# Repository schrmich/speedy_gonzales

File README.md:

# speedy_gonzales
A small unique robot plattform with AVR microcontroller programmed in C.

1	Vorwort
Der Roboter „Speedy-bot“ ist ein kleiner frei in C programmierbarer Lern Roboter. Er soll in der Lage sein, verschiedene Aufgaben selbstständig zu erledigen, dazu gehören das Lösen von Linienlabyrinthen. Dazu ist er mit einer Reihe von 5 analogen IR-Reflektions Sensoren an der Unterseite ausgestattet, sowie zwei optische Motorencoder. Zur Kommunikation wird ein HC-06 Bluetooth Modul verwendet. Als Antrieb dienen zwei DC-Getriebemotoren.
Die Elektronik ist komplett in SMD aufgebaut und als Steuercomputer werkelt ein Atmega644PA. 

2	Aufgaben/ Ziele
Hier eine kleine  Liste mit möglichen Aufgaben die Spirit bewältigen soll:
•	Einfaches Linienfolgen PID Regler mit max. Geschwindigkeit
•	Linienfolgen mit Unterbrechungen, Kreuzungen, Hindernissen, etc…
•	Joghurt Sumo
•	Fernsteuerung über PC/ Smartphone
3	Mechanik
Der Roboter hat die Abmessungen von 100x75 mm und hat zwei Antriebsräder mit zwei Stützrädern vorn und hinten. Sein Gesamtgewicht mit Akkus beläuft sich auf 85g.

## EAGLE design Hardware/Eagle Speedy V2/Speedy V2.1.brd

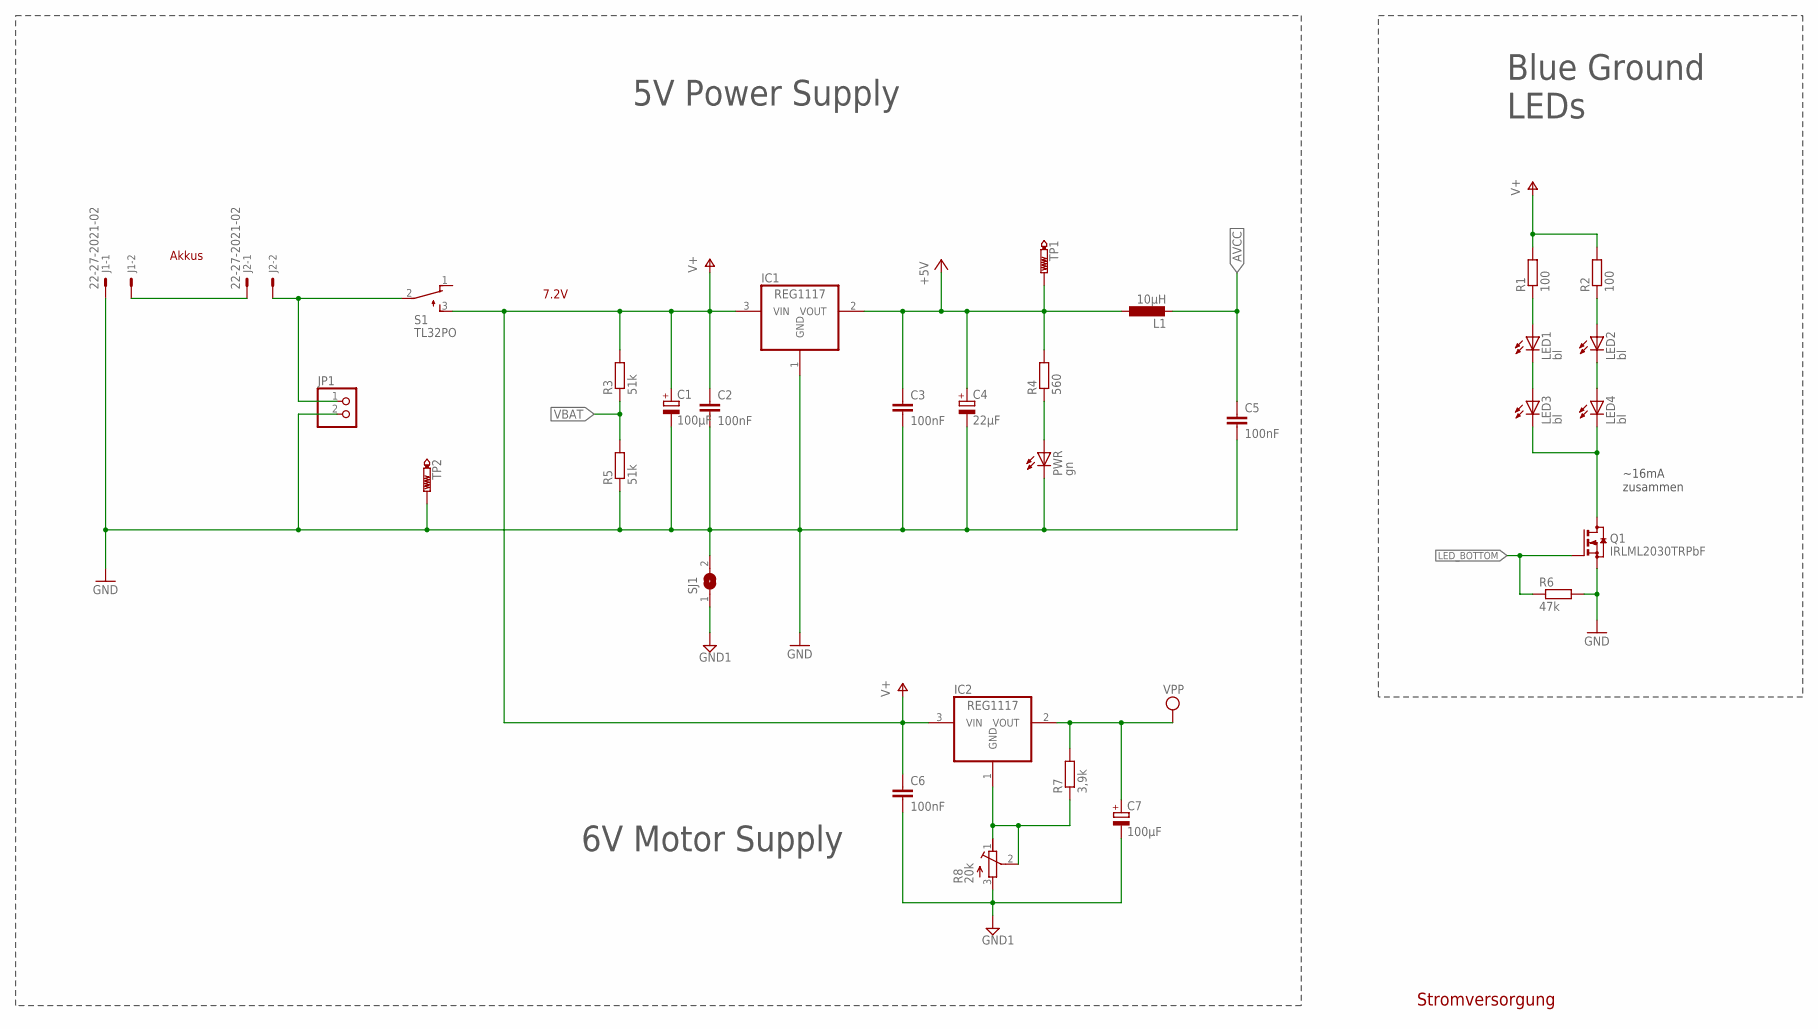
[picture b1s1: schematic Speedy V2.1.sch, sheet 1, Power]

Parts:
C1, C7: 100µF; PANASONIC_D
C2, C3, C5, C6: 100nF; C0805
C4: 22µF; PANASONIC_B
IC1, IC2: REG1117; SOT223
J1, J2: 22-27-2021-02; 6410-02
JP1: PINHD-1X2; 1X02
L1: 10µH; C1210K
LED1, LED2, LED3, LED4: bl; CHIPLED_0805
PWR: gn; CHIPLED_0805
Q1: IRLML2030TRPbF; SOT23
R1, R2: 100; R0805
R3, R5: 51k; R0805
R4: 560; R0805
R6: 47k; R0805
R7: 3,9k; R0805
R8: 20k; RTRIM3314G
S1: TL32PO; TL3XPO
SJ1: SJ
TP1: PTR1B1,27; B1,27
TP2: PTR1PAD1-13; P1-13

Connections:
+5V: C3.1, C4.+, IC1.2 (VOUT), L1.1, R4.2, TP1.TP; also elsewhere on the board
AVCC: C5.1, L1.2; also elsewhere on the board
GND: C1.-, C2.2, C3.2, C4.-, C5.2, IC1.1 (GND), J1.1, JP1.2, PWR.C, Q1.2 (S), R5.1, R6.2, SJ1.2, TP2.TP; also elsewhere on the board
GND1: C6.2, C7.-, R8.3 (A), SJ1.1; also elsewhere on the board
LED_BOTTOM: Q1.1 (G), R6.1; also elsewhere on the board
unnamed: J1.2, J2.1
unnamed: PWR.A, R4.1
unnamed: J2.2, JP1.1, S1.2
unnamed: LED3.C, LED4.C, Q1.3 (D)
unnamed: LED1.A, R1.1
unnamed: LED1.C, LED3.A
unnamed: LED2.C, LED4.A
unnamed: LED2.A, R2.1
unnamed: IC2.1 (GND), R7.1, R8.1 (E), R8.2 (S)
V+: C1.+, C2.1, C6.1, IC1.3 (VIN), IC2.3 (VIN), R1.2, R2.2, R3.2, S1.3 (S); also elsewhere on the board
VBAT: R3.1, R5.2; also elsewhere on the board
VPP: C7.+, IC2.2 (VOUT), R7.2; also elsewhere on the board

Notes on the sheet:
Stromversorgung
5V Power Supply
Blue Ground LEDs
Akkus
7.2V
~16mA zusammen
6V Motor Supply

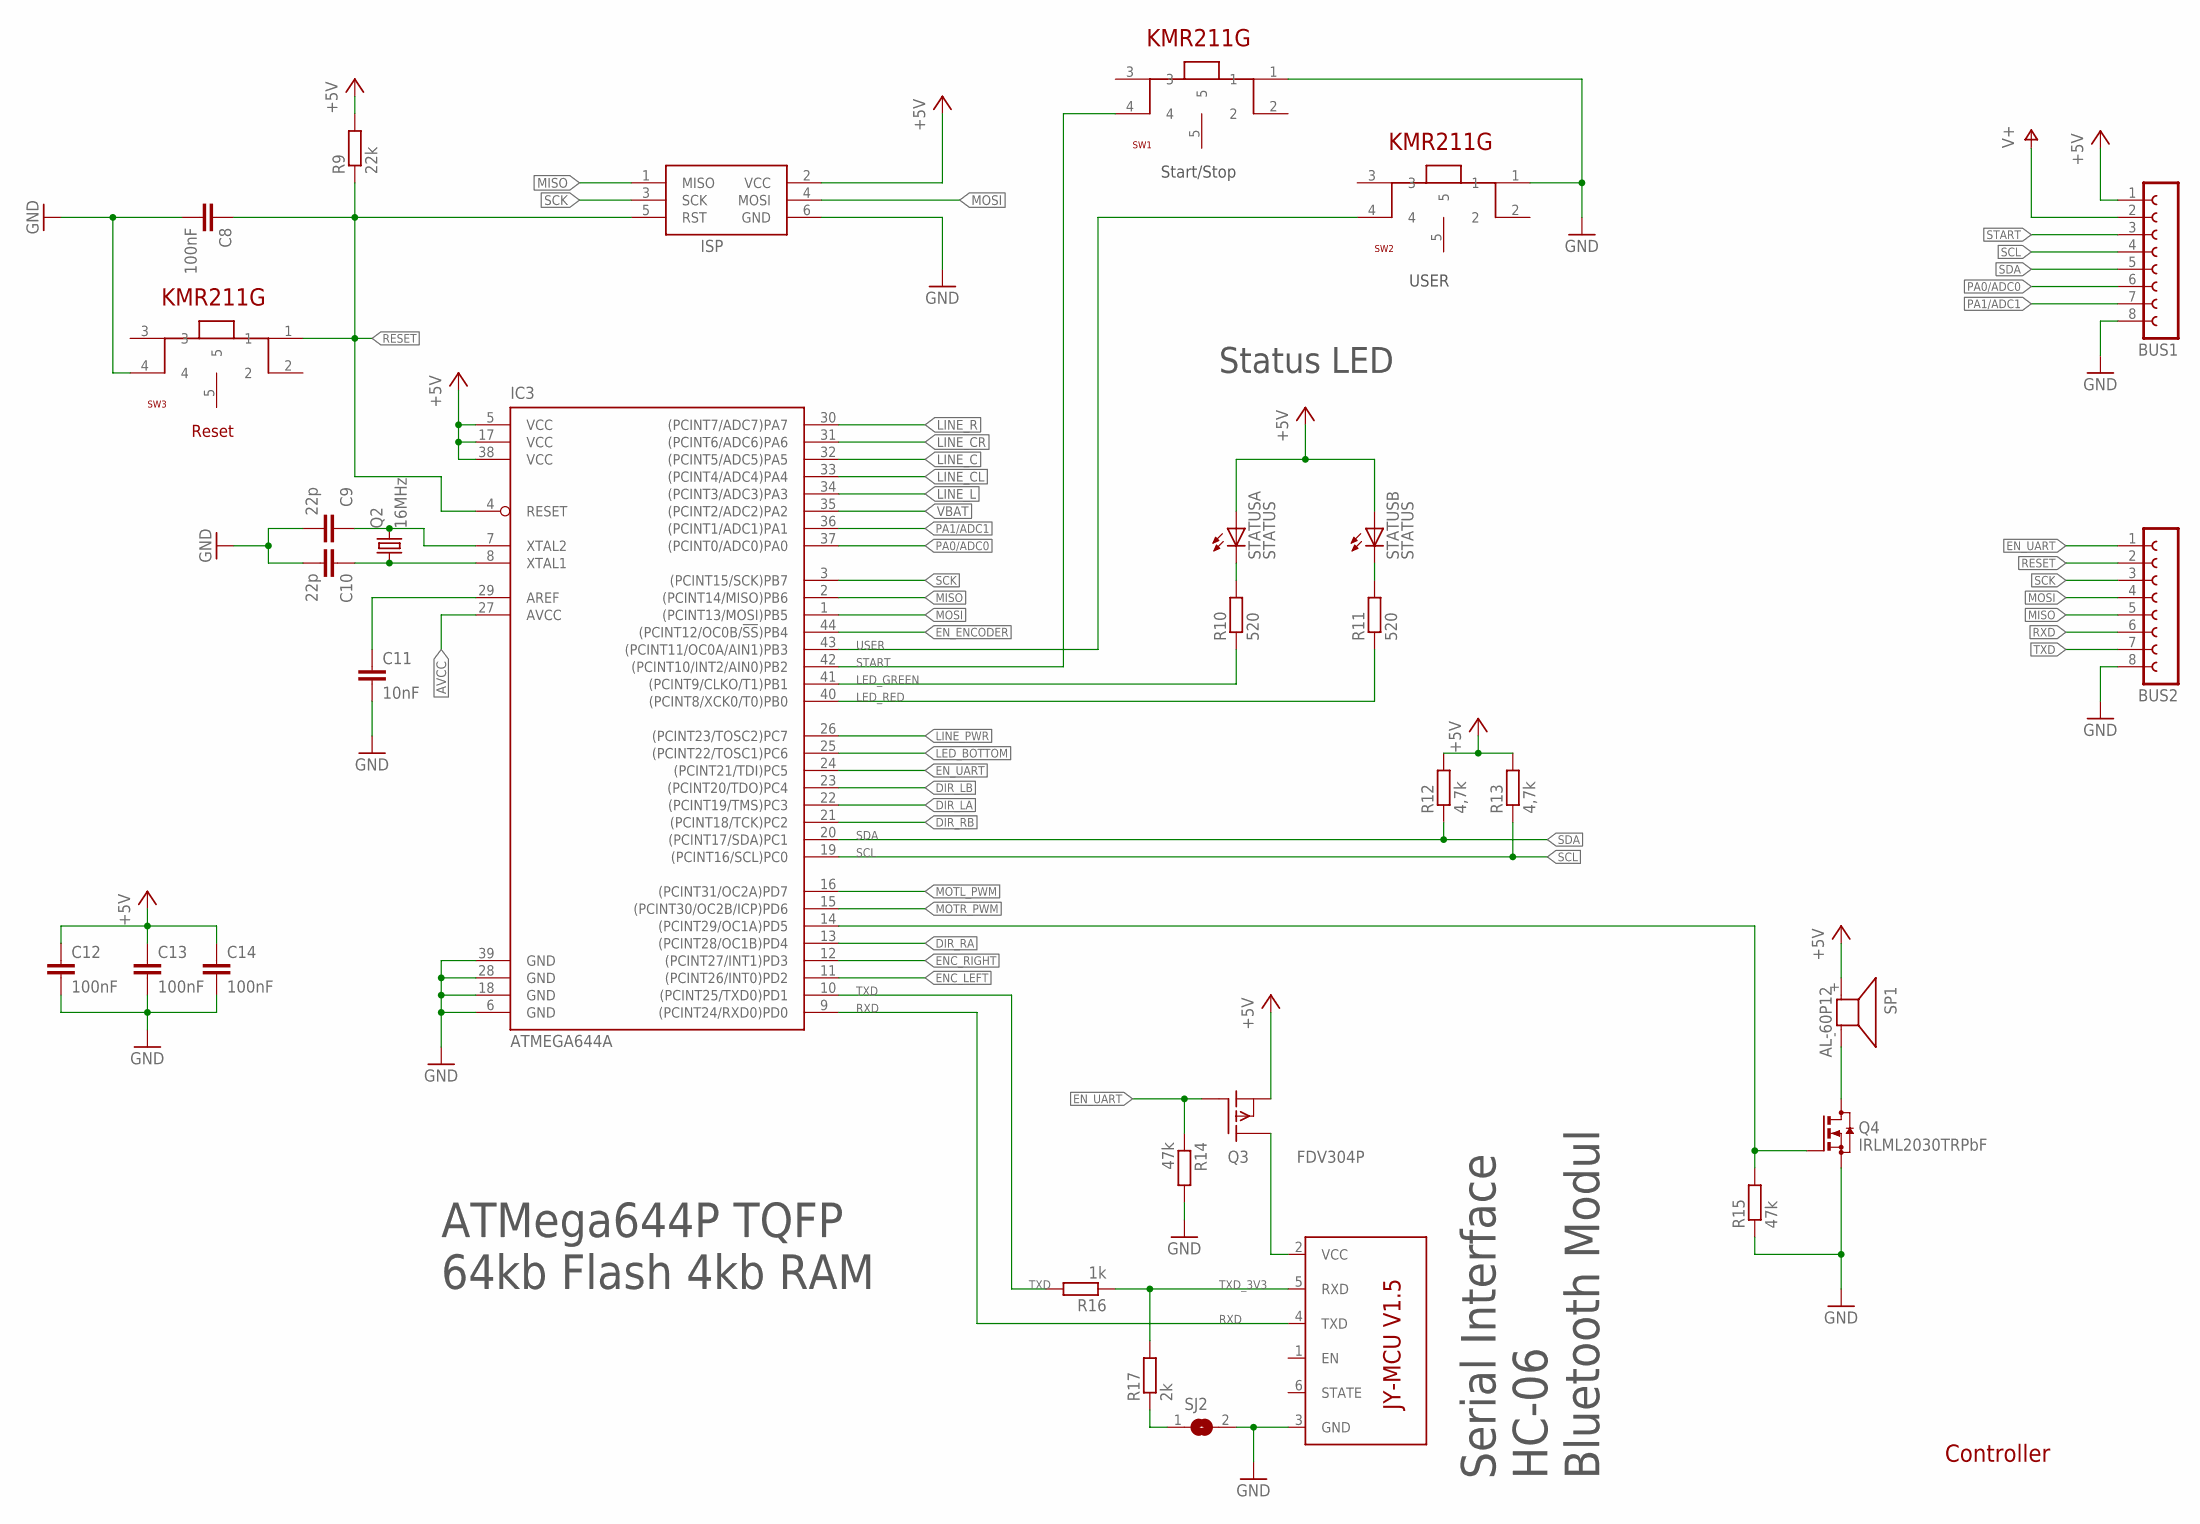
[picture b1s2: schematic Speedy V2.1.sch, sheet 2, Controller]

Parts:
BUS1, BUS2: FE08-1; FE08
C8: 100nF; C0805
C9, C10: 22p; C0603
C11: 10nF; C0603
C12, C13, C14: 100nF; C0603
IC3: ATMEGA644A; TQFP44
ISP: AVRISP-6; AVRISP
Q2: 16MHz; 7X5MMQUARZ
Q3: FDV304P; SOT23
Q4: IRLML2030TRPbF; SOT23
R9: 22k; R0805
R10, R11: 520; R0805
R12, R13: 4,7k; R0805
R14, R15: 47k; R0805
R16: 1k; R0805
R17: 2k; R0805
SJ2: SJ
SP1: AL-60P12; KSS1201
STATUS: STATUS; P-LCC4-0
SW1, SW2, SW3: KMR211G_SWITCH
U1: BT_BOARD

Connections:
+5V: BUS1.1, C12.1, C13.1, C14.1, IC3.5 (VCC), IC3.17 (VCC), IC3.38 (VCC), ISP.2 (VCC), Q3.S, R9.2, R12.2, R13.2, SP1.+ (1), STATUS.2 (A), STATUS.4 (A); also elsewhere on the board
AVCC: IC3.27 (AVCC); also elsewhere on the board
BUZZER: IC3.14 ((PCINT29/OC1A)PD5), Q4.1 (G), R15.2
DIR_LA: IC3.22 ((PCINT19/TMS)PC3); also elsewhere on the board
DIR_LB: IC3.23 ((PCINT20/TDO)PC4); also elsewhere on the board
DIR_RA: IC3.13 ((PCINT28/OC1B)PD4); also elsewhere on the board
DIR_RB: IC3.21 ((PCINT18/TCK)PC2); also elsewhere on the board
ENC_LEFT: IC3.11 ((PCINT26/INT0)PD2); also elsewhere on the board
ENC_RIGHT: IC3.12 ((PCINT27/INT1)PD3); also elsewhere on the board
EN_ENCODER: IC3.44 ((PCINT12/OC0B/!SS!)PB4); also elsewhere on the board
EN_UART: BUS2.1, IC3.24 ((PCINT21/TDI)PC5), Q3.G, R14.1
GND: BUS1.8, BUS2.8, C8.2, C9.2, C10.2, C11.2, C12.2, C13.2, C14.2, IC3.6 (GND), IC3.18 (GND), IC3.28 (GND), IC3.39 (GND), ISP.6 (GND), Q4.2 (S), R14.2, R15.1, SJ2.2, SW1.1, SW2.1, SW3.4, U1.3 (GND); also elsewhere on the board
LED_BOTTOM: IC3.25 ((PCINT22/TOSC1)PC6); also elsewhere on the board
LED_GREEN: IC3.41 ((PCINT9/CLKO/T1)PB1), R10.1
LED_RED: IC3.40 ((PCINT8/XCK0/T0)PB0), R11.1
LINE_C: IC3.32 ((PCINT5/ADC5)PA5); also elsewhere on the board
LINE_CL: IC3.33 ((PCINT4/ADC4)PA4); also elsewhere on the board
LINE_CR: IC3.31 ((PCINT6/ADC6)PA6); also elsewhere on the board
LINE_L: IC3.34 ((PCINT3/ADC3)PA3); also elsewhere on the board
LINE_PWR: IC3.26 ((PCINT23/TOSC2)PC7); also elsewhere on the board
LINE_R: IC3.30 ((PCINT7/ADC7)PA7); also elsewhere on the board
MISO: BUS2.5, IC3.2 ((PCINT14/MISO)PB6), ISP.1 (MISO)
MOSI: BUS2.4, IC3.1 ((PCINT13/MOSI)PB5), ISP.4 (MOSI)
MOTL_PWM: IC3.16 ((PCINT31/OC2A)PD7); also elsewhere on the board
MOTR_PWM: IC3.15 ((PCINT30/OC2B/ICP)PD6); also elsewhere on the board
unnamed: Q4.3 (D), SP1.- (2)
unnamed: R10.2, STATUS.1 (C)
unnamed: C11.1, IC3.29 (AREF)
unnamed: R17.1, SJ2.1
unnamed: R11.2, STATUS.3 (C)
unnamed: Q3.D, U1.2 (VCC)
unnamed: C9.1, IC3.7 (XTAL2), Q2.P$3 (2)
unnamed: C10.1, IC3.8 (XTAL1), Q2.P$1 (1)
PA0/ADC0: BUS1.6, IC3.37 ((PCINT0/ADC0)PA0)
PA1/ADC1: BUS1.7, IC3.36 ((PCINT1/ADC1)PA1)
RESET: BUS2.2, C8.1, IC3.4 (RESET), ISP.5 (RST), R9.1, SW3.1; also elsewhere on the board
RXD: BUS2.6, IC3.9 ((PCINT24/RXD0)PD0), U1.4 (TXD)
SCK: BUS2.3, IC3.3 ((PCINT15/SCK)PB7), ISP.3 (SCK)
SCL: BUS1.4, IC3.19 ((PCINT16/SCL)PC0), R13.1
SDA: BUS1.5, IC3.20 ((PCINT17/SDA)PC1), R12.1
START: BUS1.3, IC3.42 ((PCINT10/INT2/AIN0)PB2), SW1.4
TXD: BUS2.7, IC3.10 ((PCINT25/TXD0)PD1), R16.2
TXD_3V3: R16.1, R17.2, U1.5 (RXD)
USER: IC3.43 ((PCINT11/OC0A/AIN1)PB3), SW2.4
V+: BUS1.2; also elsewhere on the board
VBAT: IC3.35 ((PCINT2/ADC2)PA2); also elsewhere on the board

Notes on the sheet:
Controller
Start/Stop
Reset
Serial Interface HC-06 Bluetooth Modul
ATMega644P TQFP 64kb Flash 4kb RAM
USER
Status LED

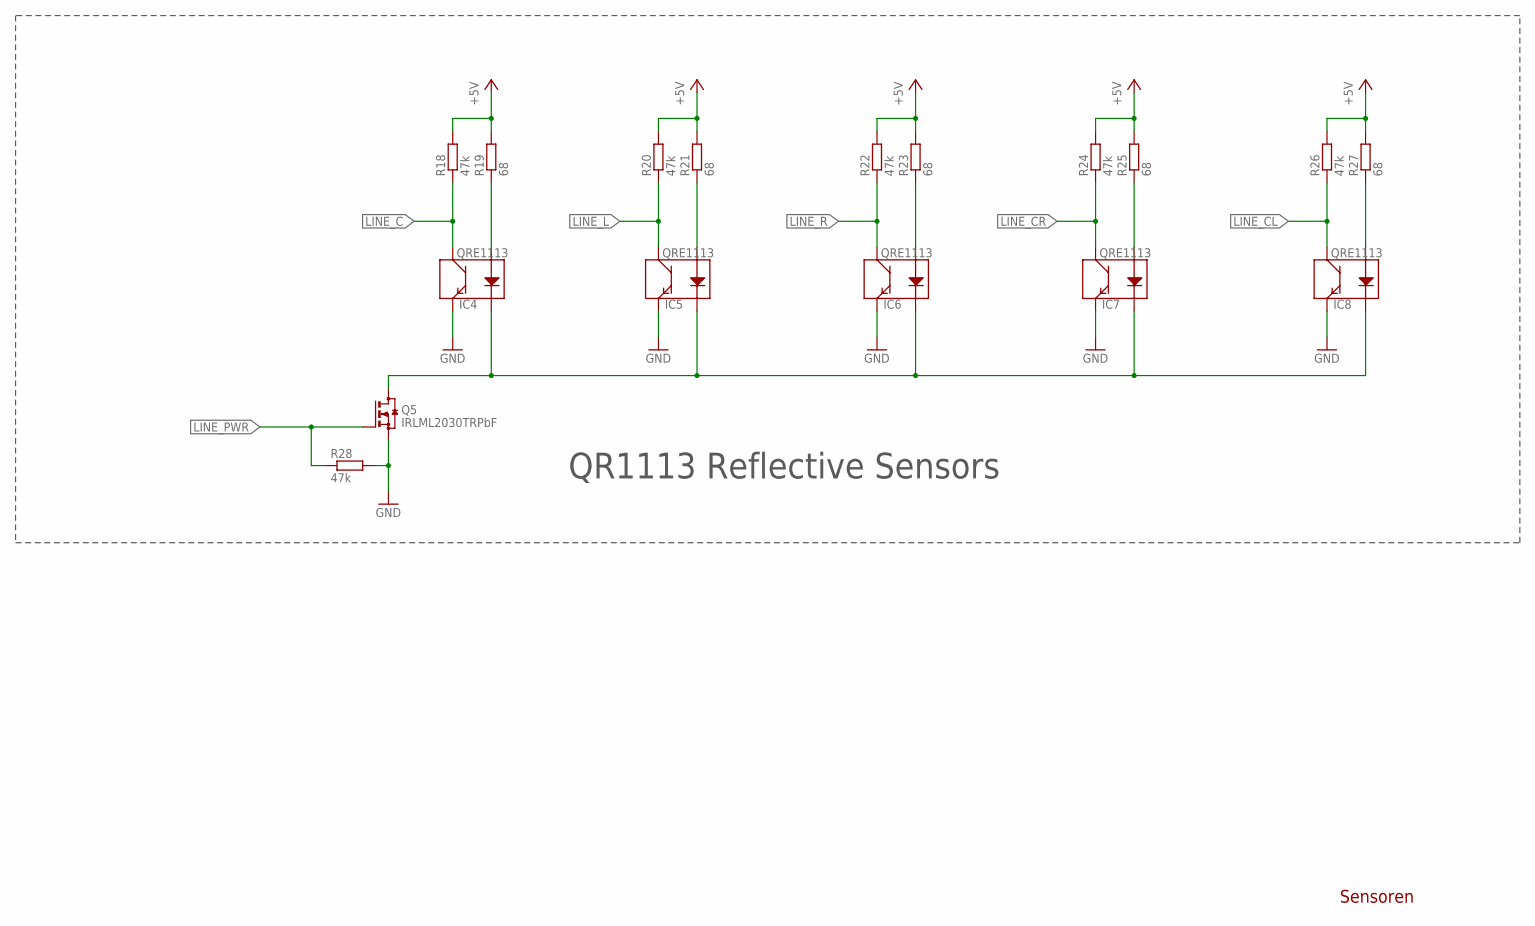
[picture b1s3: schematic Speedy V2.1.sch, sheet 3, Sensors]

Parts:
IC4, IC5, IC6, IC7, IC8: QRE1113
Q5: IRLML2030TRPbF; SOT23
R18, R20, R22, R24, R26, R28: 47k; R0805
R19, R21, R23, R25, R27: 68; R0805

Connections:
+5V: R18.2, R19.2, R20.2, R21.2, R22.2, R23.2, R24.2, R25.2, R26.2, R27.2; also elsewhere on the board
GND: IC4.4 (E), IC5.4 (E), IC6.4 (E), IC7.4 (E), IC8.4 (E), Q5.2 (S), R28.2; also elsewhere on the board
LINE_C: IC4.3 (C), R18.1; also elsewhere on the board
LINE_CL: IC8.3 (C), R26.1; also elsewhere on the board
LINE_CR: IC7.3 (C), R24.1; also elsewhere on the board
LINE_L: IC5.3 (C), R20.1; also elsewhere on the board
LINE_PWR: Q5.1 (G), R28.1; also elsewhere on the board
LINE_R: IC6.3 (C), R22.1; also elsewhere on the board
unnamed: IC4.2 (K), IC5.2 (K), IC6.2 (K), IC7.2 (K), IC8.2 (K), Q5.3 (D)
unnamed: IC5.1 (A), R21.1
unnamed: IC4.1 (A), R19.1
unnamed: IC6.1 (A), R23.1
unnamed: IC7.1 (A), R25.1
unnamed: IC8.1 (A), R27.1

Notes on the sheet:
Sensoren
QR1113 Reflective Sensors

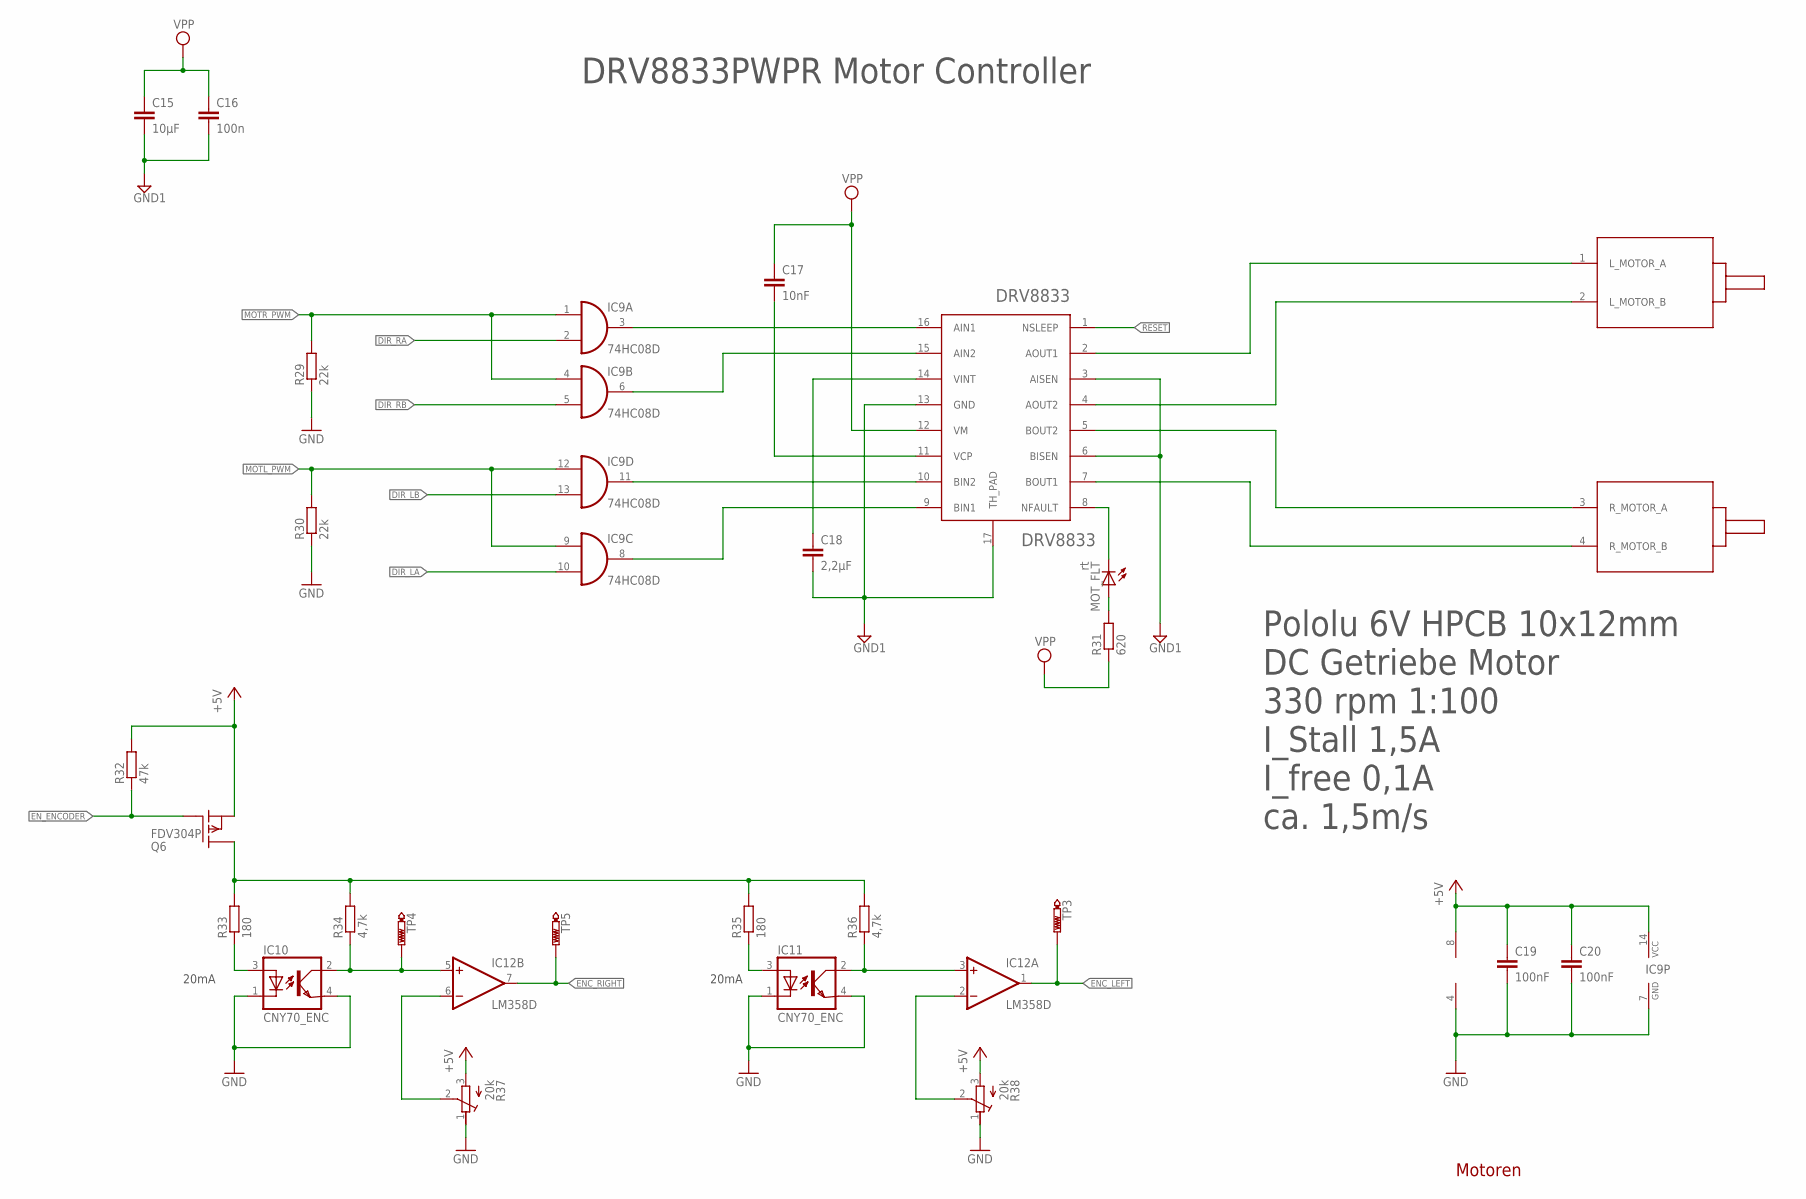
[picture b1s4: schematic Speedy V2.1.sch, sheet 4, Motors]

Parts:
C15: 10µF; C1206
C16: 100n; C0805
C17: 10nF; C0805
C18: 2,2µF; C1206
C19, C20: 100nF; C0805
IC9: 74HC08D; SO14
IC10, IC11: CNY70_ENC
IC12: LM358D; SO08
MOT_FLT: rt; CHIP-LED0805
Q6: FDV304P; SOT23
R29, R30: 22k; R0805
R31: 620; R0805
R32: 47k; R0805
R33, R35: 180; R0805
R34, R36: 4,7k; R0805
R37, R38: 20k; RTRIM3314G
TP3, TP4, TP5: PTR1B1,27; B1,27
U2: DRV8833; SOP65P640X120-17N
U$1: SPEEDY_MOTOR_MOUNT; FUTURA_V1.0_MOTOT_MOUNT

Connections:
+5V: C19.1, C20.1, IC9.14 (VCC), IC12.8 (V+), Q6.S, R32.2, R37.3 (A), R38.3 (A); also elsewhere on the board
DIR_LA: IC9.10 (I1); also elsewhere on the board
DIR_LB: IC9.13 (I1); also elsewhere on the board
DIR_RA: IC9.2 (I1); also elsewhere on the board
DIR_RB: IC9.5 (I1); also elsewhere on the board
ENC_LEFT: IC12.1 (OUT), TP3.TP; also elsewhere on the board
ENC_RIGHT: IC12.7 (OUT), TP5.TP; also elsewhere on the board
EN_ENCODER: Q6.G, R32.1; also elsewhere on the board
GND: C19.2, C20.2, IC9.7 (GND), IC10.1 (CATH.), IC10.4 (E), IC11.1 (CATH.), IC11.4 (E), IC12.4 (V-), R29.1, R30.1, R37.1 (E), R38.1 (E); also elsewhere on the board
GND1: C15.2, C16.2, C18.2, U2.3 (AISEN), U2.6 (BISEN), U2.13 (GND), U2.17 (TH_PAD); also elsewhere on the board
MOTL_PWM: IC9.9 (I0), IC9.12 (I0), R30.2; also elsewhere on the board
MOTR_PWM: IC9.1 (I0), IC9.4 (I0), R29.2; also elsewhere on the board
unnamed: C18.1, U2.14 (VINT)
unnamed: C17.2, U2.11 (VCP)
unnamed: IC11.3 (A), R35.1
unnamed: IC11.2 (COL), IC12.3 (+IN), R36.1
unnamed: IC10.3 (A), R33.1
unnamed: U2.5 (BOUT2), U$1.3 (R_MOTOR_A)
unnamed: MOT_FLT.A, R31.2
unnamed: MOT_FLT.C, U2.8 (NFAULT)
unnamed: IC9.3 (O), U2.16 (AIN1)
unnamed: IC9.6 (O), U2.15 (AIN2)
unnamed: IC9.11 (O), U2.10 (BIN2)
unnamed: IC9.8 (O), U2.9 (BIN1)
unnamed: IC10.2 (COL), IC12.5 (+IN), R34.1, TP4.TP
unnamed: IC12.6 (-IN), R37.2 (S)
unnamed: U2.7 (BOUT1), U$1.4 (R_MOTOR_B)
unnamed: U2.4 (AOUT2), U$1.2 (L_MOTOR_B)
unnamed: U2.2 (AOUT1), U$1.1 (L_MOTOR_A)
unnamed: IC12.2 (-IN), R38.2 (S)
unnamed: Q6.D, R33.2, R34.2, R35.2, R36.2
RESET: U2.1 (NSLEEP); also elsewhere on the board
VPP: C15.1, C16.1, C17.1, R31.1, U2.12 (VM); also elsewhere on the board

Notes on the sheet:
Motoren
DRV8833PWPR Motor Controller
Pololu 6V HPCB 10x12mm DC Getriebe Motor 330 rpm 1:100 I_Stall 1,5A I_free 0,1A ca. 1,5m/s
20mA

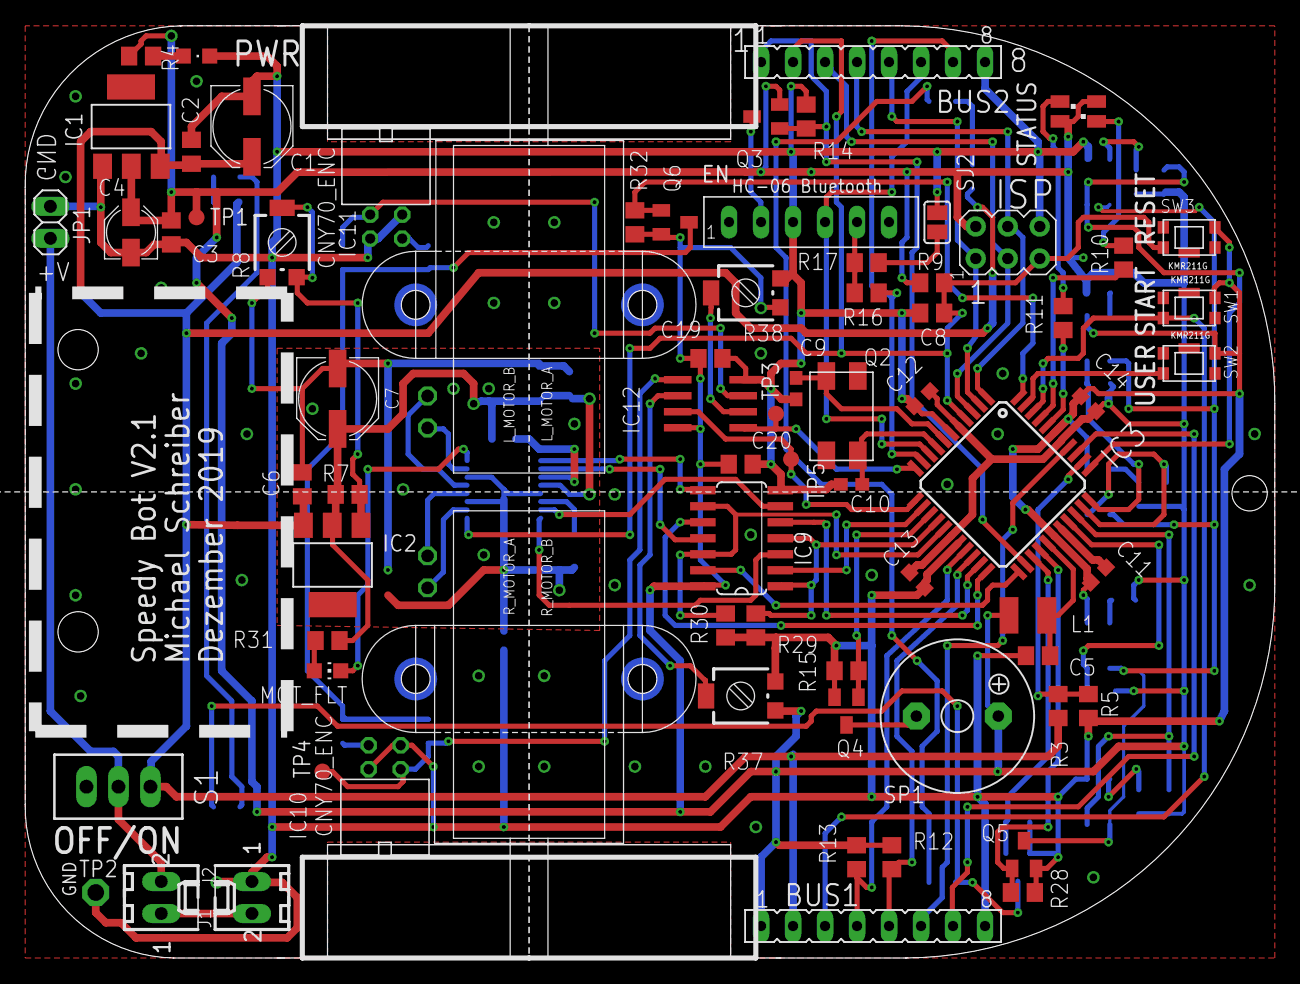
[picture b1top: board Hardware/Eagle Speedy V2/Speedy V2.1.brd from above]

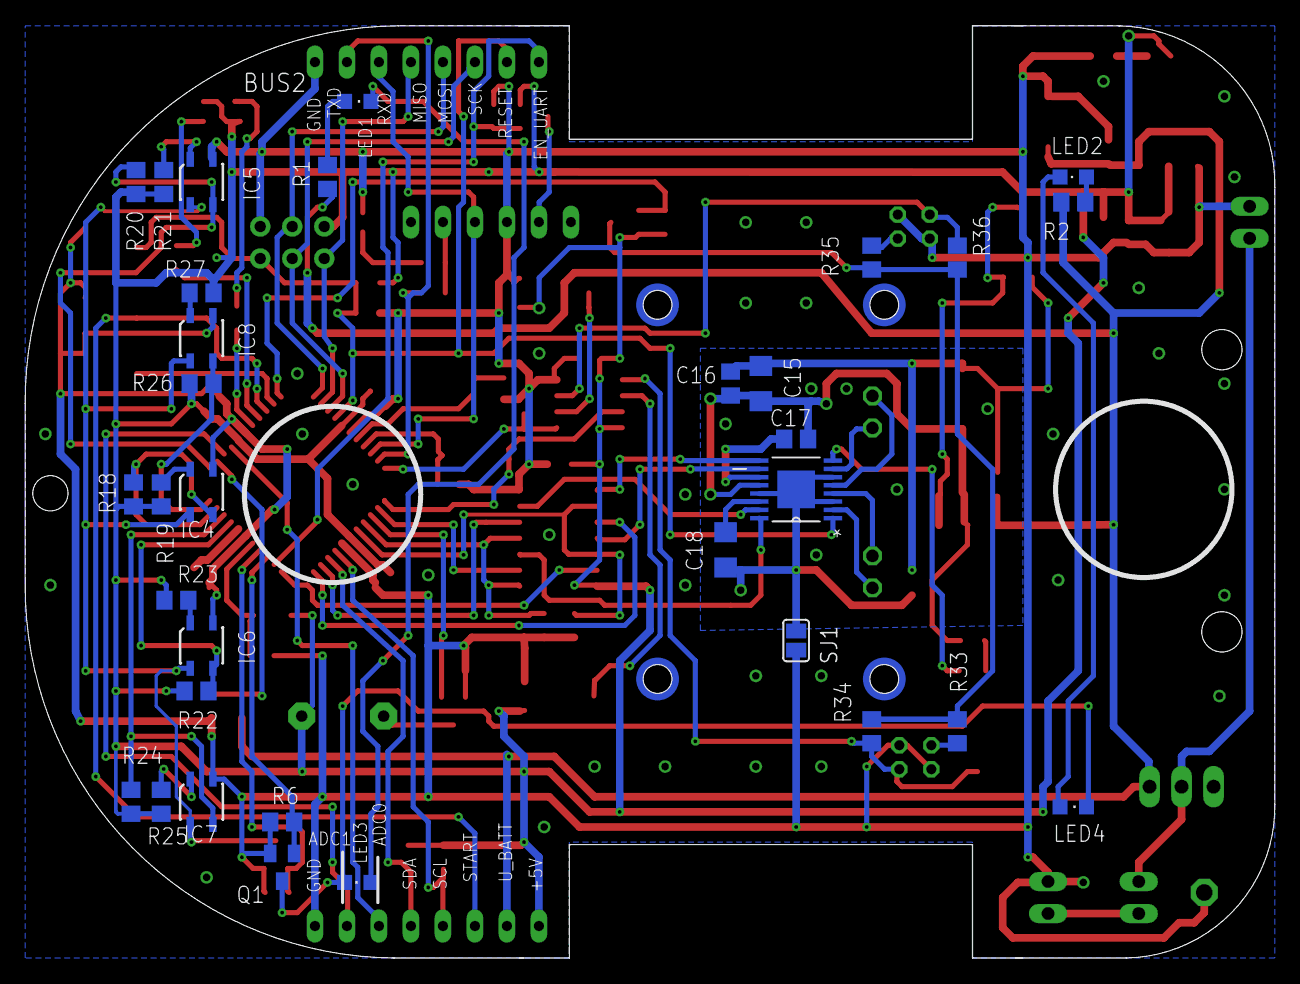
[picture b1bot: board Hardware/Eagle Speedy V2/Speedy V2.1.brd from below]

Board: 2 copper layers, 99.1 x 74.0 mm, 105 parts (33 on the bottom side), 82 nets.

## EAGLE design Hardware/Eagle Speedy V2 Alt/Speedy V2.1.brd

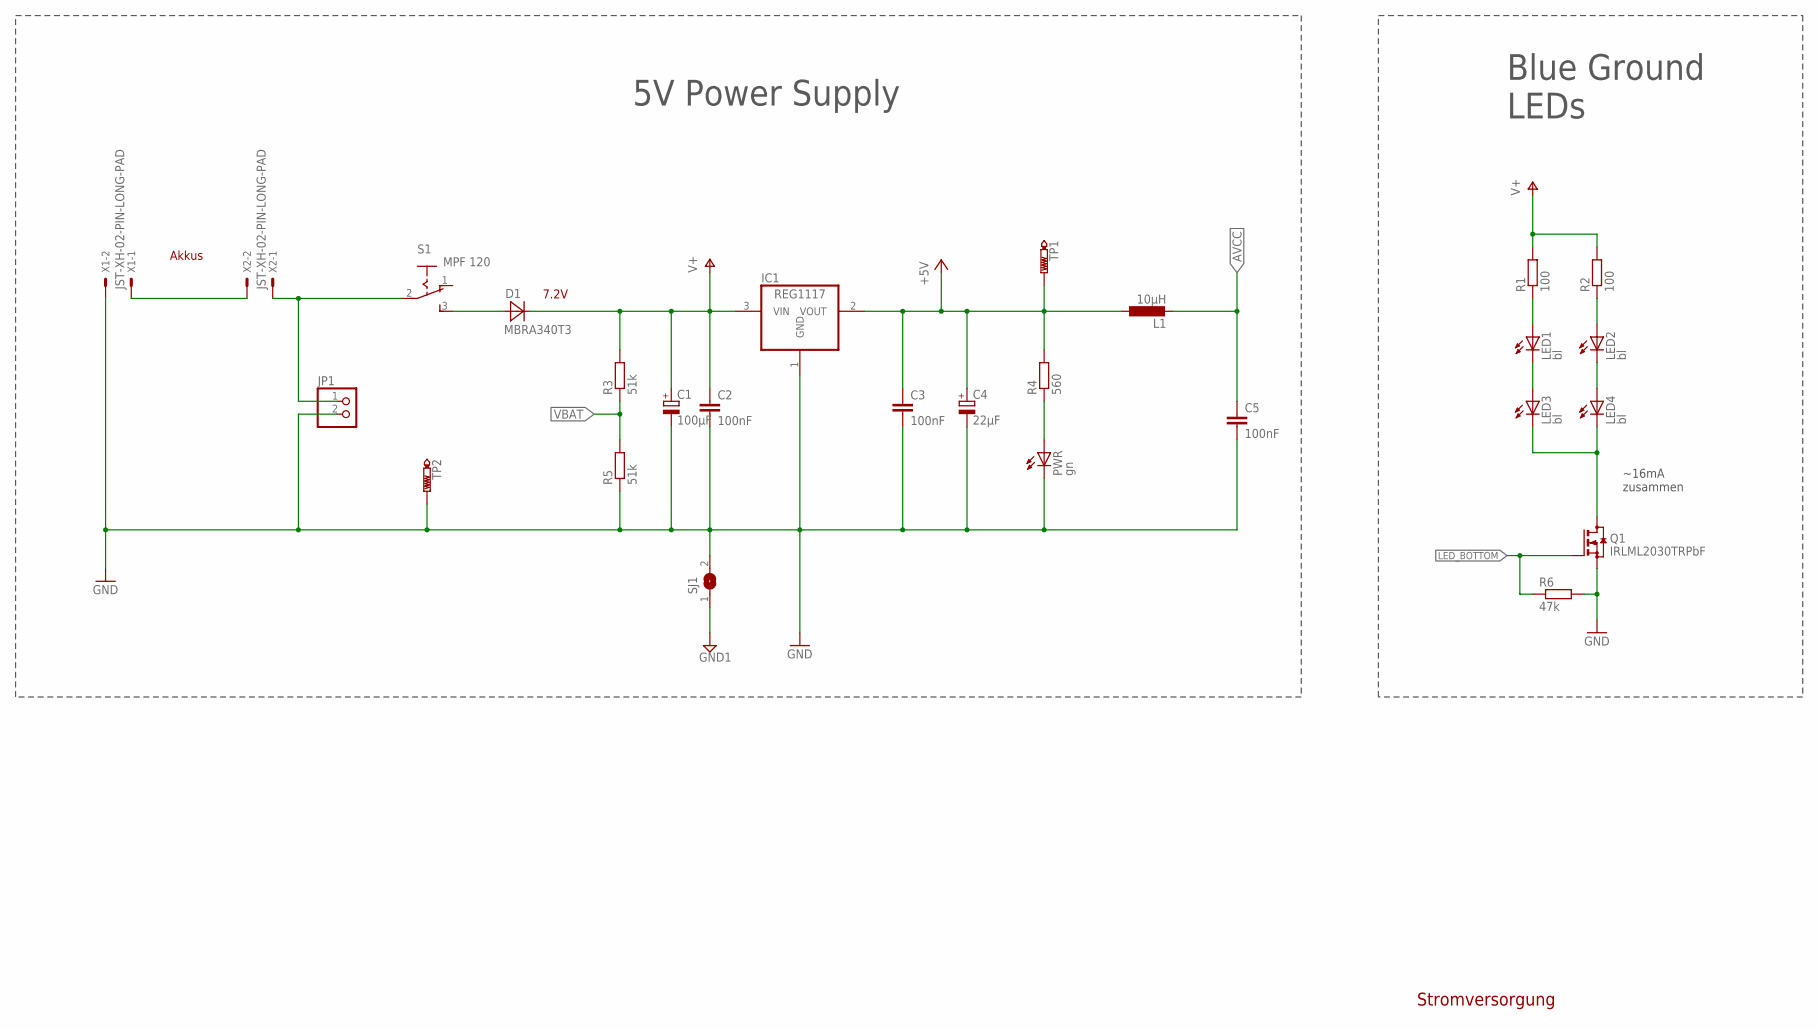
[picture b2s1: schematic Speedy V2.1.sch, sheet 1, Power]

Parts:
C1: 100µF; PANASONIC_D
C2, C3, C5: 100nF; C0805
C4: 22µF; PANASONIC_B
D1: MBRA340T3; SMA
IC1: REG1117; SOT223
JP1: PINHD-1X2; 1X02
L1: 10µH; C1210K
LED1, LED2, LED3, LED4: bl; CHIPLED_0805
PWR: gn; CHIPLED_0805
Q1: IRLML2030TRPbF; SOT23
R1, R2: 100; R0805
R3, R5: 51k; R0805
R4: 560; R0805
R6: 47k; R0805
S1: MPF 120; 255SB
SJ1: SJ
TP1: PTR1B1,27; B1,27
TP2: PTR1PAD1-13; P1-13
X1, X2: JST-XH-02-PIN-LONG-PAD; JST-XH-02-PACKAGE-LONG-PAD

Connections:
+5V: C3.1, C4.+, IC1.2 (VOUT), L1.1, R4.2, TP1.TP; also elsewhere on the board
AVCC: C5.1, L1.2; also elsewhere on the board
GND: C1.-, C2.2, C3.2, C4.-, C5.2, IC1.1 (GND), JP1.2, PWR.C, Q1.2 (S), R5.1, R6.2, SJ1.2, TP2.TP, X1.2; also elsewhere on the board
GND1: SJ1.1; also elsewhere on the board
LED_BOTTOM: Q1.1 (G), R6.1; also elsewhere on the board
unnamed: X1.1, X2.2
unnamed: PWR.A, R4.1
unnamed: JP1.1, S1.2, X2.1
unnamed: LED3.C, LED4.C, Q1.3 (D)
unnamed: D1.A, S1.3 (S)
unnamed: LED1.A, R1.1
unnamed: LED1.C, LED3.A
unnamed: LED2.C, LED4.A
unnamed: LED2.A, R2.1
V+: C1.+, C2.1, D1.C, IC1.3 (VIN), R1.2, R2.2, R3.2; also elsewhere on the board
VBAT: R3.1, R5.2; also elsewhere on the board

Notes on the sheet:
Stromversorgung
5V Power Supply
Blue Ground LEDs
Akkus
7.2V
~16mA zusammen
